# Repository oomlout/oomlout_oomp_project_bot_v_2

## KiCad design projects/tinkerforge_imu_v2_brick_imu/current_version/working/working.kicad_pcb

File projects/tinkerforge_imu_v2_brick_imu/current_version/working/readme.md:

# imu_v2_brick
 
## summary 
* id: tinkerforge_imu_v2_brick_imu
* user: tinkerforge
* name: imu_v2_brick
* board: imu
* repo: https://github.com/Tinkerforge/imu-v2-brick
* src_file_repo_kicad_pcb: hardware/V3/imu.kicad_pcb
* src_file_repo_kicad_pcb_link: https://github.com/Tinkerforge/imu-v2-brick/tree/master/hardware/V3/imu.kicad_pcb

* src_file_repo_sch: 
* src_file_repo_sch_link: https://github.com/Tinkerforge/imu-v2-brick/tree/master/
* full details link: https://github.com/oomlout/oomlout_oomp_project_bot_v_2/tree/main/projects/tinkerforge_imu_v2_brick_imu/current_version/working

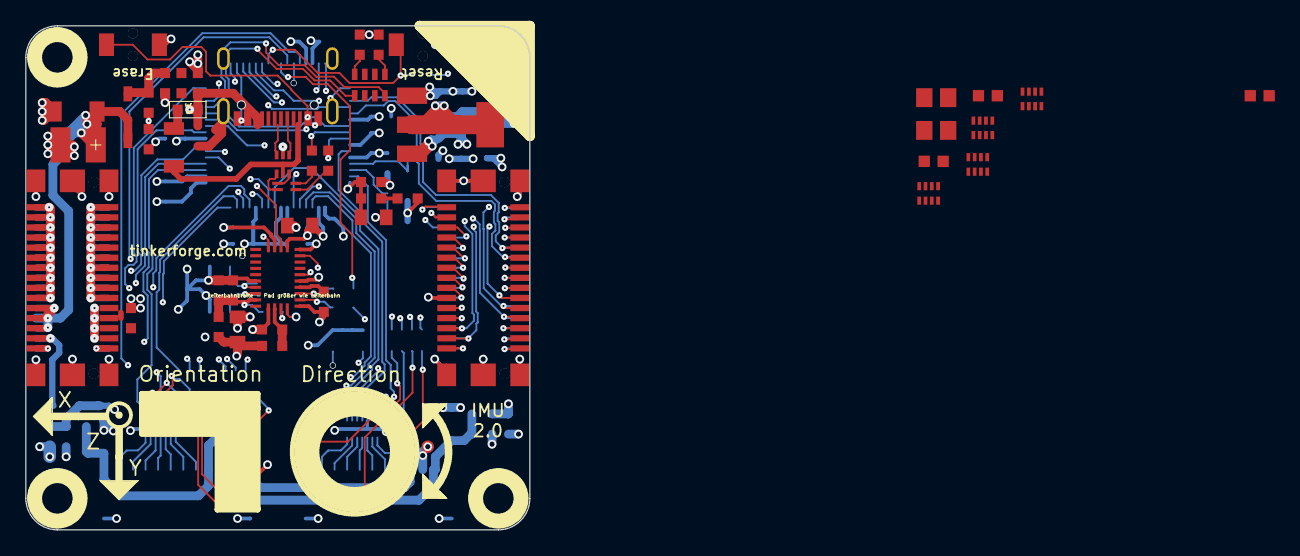
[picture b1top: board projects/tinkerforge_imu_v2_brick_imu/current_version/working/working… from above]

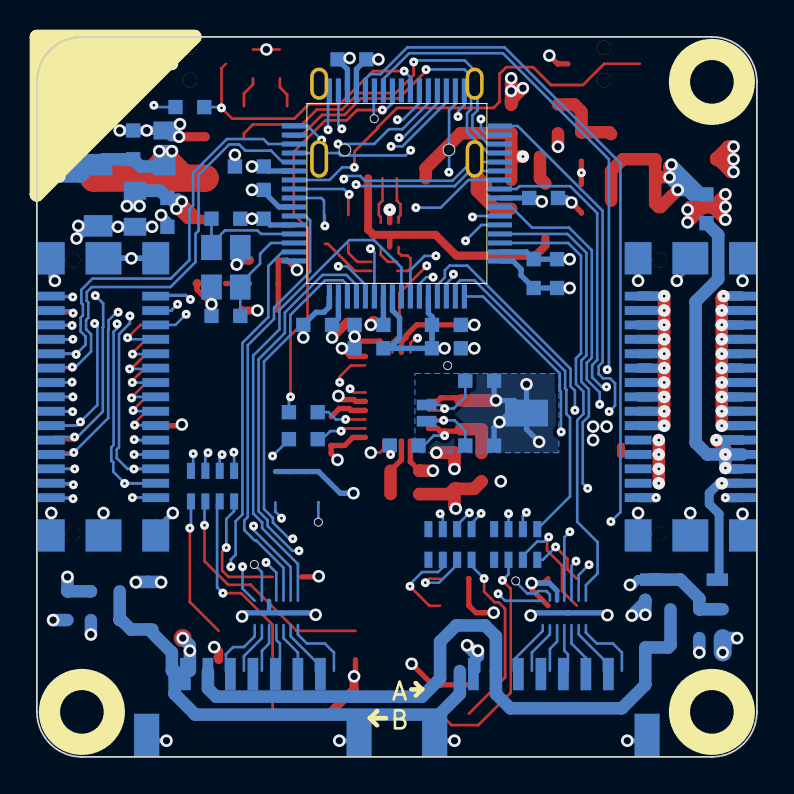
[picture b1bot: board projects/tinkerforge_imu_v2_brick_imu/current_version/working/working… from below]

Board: 4 copper layers, 40.0 x 40.0 mm, 96 parts (36 on the bottom side), 113 nets.

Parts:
C1, C2: DNP; C0603
C3: 1µF; 0603
C4: 1µF; C0603
C5, C6: 22pF; C0603
C7, C8, C14, C17, C18, C19, C20, C22, C23, C24, C26, C27, C29, C30: 100nF; C0603
C9: 6.8nF; C0603
C10: 120nF; C0603
C11: 4.7µF; C0805
C12: 100µF; 3528-21
C13, C16: 10µF; C0805
C15, C28: 4.7µF; C0603
C21: 2.2µF; C0603
C25: 10µF/10V; C0805
C31, C33: 10uF; C0805E
C32, C34: 100nF; C0603F
CP1, CP2: 220pF; 4X0402
D1, D3, D5, D7: blue; D0603
D2, D4, D6, D8: red; D0603
D9, D10, D11, D12: green; D0603
D13, D14: B0520LW-7-F; SOD-123
D15: Z5V; MiniMelf
D16: Z3.3V; MiniMelf
F1: PTC; C1206
FB1, FB3, FB4: FB; C0603
J1: USB-C
J2, J3, J4, J5: DRILL; DRILL_NP
J6, J8: STACK-UP-LOW; BTB08-ACS-TOP
J7, J9: STACK-DOWN; BTB08-ACS-BTM
L1: 744230900; WE-CNSW-0603
L2, L3: INDUCTOR; C0603
L4: LBR2012T100K; C0805
P1, P2: CON-SENSOR2
R1, R2: 27; R0603
R3: 0; R0603
R4: 47k; R0603
R5: 68k; R0603
R6: 10k; R0603
R7, R8: DNP; R0603
R9: 1k; R0603
R10: 1R0; R0603
R11: 56k; R0603F
RP1, RP2, RP3, RP4: 1k; 0603X4
RP5, RP6: 82; 4X0402
SW1: Reset; TACT-SWITCH
SW2: Erase; TACT-SWITCH
U1: AT91SAM3SXB; LQFP64
U2: 82400152; SOT563-SPEC
U3: BNO055; LGA28_5832
U4: LD1117; SOT-223
X1: 16Mhz; CRYSTAL_3225
X2: 32.768kHz; AB26TRQ

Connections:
3V3: C11.1, C13.1, C14.1, C15.1, C17.1, C19.1, C20.1, C25.1, C27.1, C30.1, C33.1, C34.1, D1.1, D2.1, D3.1, D4.1, D5.1, D6.1, D7.1, D8.1, D9.1, D10.1, D11.1, D12.1, D13.1, D16.2, J6.20, L2.2, L3.2, P1.3, P2.3, SW2.2, U1.1, U1.7, U1.18, U1.45, U1.58, U4.2
AGND: C3.2, J1.5, R3.2, U2.2
BNO-ADR-SELECT: U1.34, U3.17
BNO-BOOT: R6.2, U1.38, U3.4
BNO-INT: U1.26, U3.14
BNO-PIN7: R7.1, U1.52
BNO-PIN8: R8.1, U1.41
BNO-nRESET: U1.35, U3.11
GND: C1.2, C2.2, C4.2, C5.2, C6.2, C7.2, C8.2, C9.2, C10.2, C11.2, C12.2, C13.2, C14.2, C15.2, C16.2, C17.2, C18.2, C19.2, C20.2, C21.2, C22.2, C23.2, C24.2, C25.2, C26.2, C27.2, C28.2, C29.2, C30.2, C31.2, C32.2, C33.2, C34.2, CP1.5, CP1.6, CP1.7, CP1.8, CP2.5, CP2.6, CP2.7, CP2.8, D15.1, D16.1, FB3.1, J6.EP, J7.EP, J8.EP, J9.EP, P1.2, P1.EP, P2.2, P2.EP, R3.1, R5.1, SW1.2, U1.2, U1.17, U1.43, U1.46, U1.60, U3.2, U3.5, U3.6, U3.10, U3.15, U3.16, U3.18, U3.25, U4.1, X1.3, X2.3
LED-DEG-1: RP4.1, U1.20
LED-DEG-2: RP4.3, U1.37
LED-DEG-3: RP4.4, U1.48
LED-DEG-4: RP4.2, U1.32
LED-XYZ-XA: RP2.1, U1.15
LED-XYZ-XB: RP2.2, U1.13
LED-XYZ-YA: RP2.3, U1.23
LED-XYZ-YB: RP3.1, U1.16
LED-XYZ-ZA: RP3.2, U1.25
LED-XYZ-ZB: RP3.3, U1.42
unnamed: C3.1, F1.2, FB1.2
unnamed: C5.1, U3.27, X2.2
unnamed: C6.1, U3.26, X2.1
unnamed: C7.1, U3.9
unnamed: C8.1, L3.1, U3.3
unnamed: C9.1, C10.1, L2.1, R6.1, U3.28
unnamed: C21.1, C22.1, C23.1, C24.1, C26.1, L4.1, U1.8, U1.12, U1.24, U1.54
unnamed: C28.1, R10.1
unnamed: C29.1, L4.2, R10.2, U1.64
unnamed: CP1.1, P1.4, RP5.8
unnamed: CP1.2, P1.5, RP5.7
unnamed: CP1.3, P1.6, RP5.6
unnamed: CP2.1, P2.4, RP6.8
unnamed: CP2.2, P2.5, RP6.7
unnamed: CP2.3, P2.6, RP6.6
unnamed: D1.2, RP1.1
unnamed: D2.2, RP1.4
unnamed: D3.2, RP2.8
unnamed: D4.2, RP2.7
unnamed: D5.2, RP2.6
unnamed: D6.2, RP3.8
unnamed: D7.2, RP3.7
unnamed: D8.2, RP3.6
unnamed: D9.2, RP4.8
unnamed: D10.2, RP4.7
unnamed: D11.2, RP4.6
unnamed: D12.2, RP4.5
unnamed: D13.2, J8.28, J9.28
unnamed: F1.1, J1.1, R11.2, U2.5
unnamed: FB3.2, J8.21, J8.23, J8.25, J8.27, J9.21, J9.23, J9.25, J9.27
unnamed: FB4.1, J8.22, J8.24, J8.26, J9.22, J9.24, J9.26
unnamed: J1.2, U2.1
unnamed: J1.3, U2.3
unnamed: J1.4, R11.1
unnamed: J6.6, J7.8
unnamed: J6.7, J7.7, R9.1
unnamed: J6.8, J7.10
unnamed: J6.10, J7.12
unnamed: J6.12, J7.14
unnamed: J6.13, J7.13
unnamed: J6.14, J7.16
unnamed: J6.15, J7.15
unnamed: J6.16, J7.18
unnamed: J6.17, J7.17
unnamed: J6.18, J7.20
unnamed: J6.22, J7.22
unnamed: J6.24, J7.24
unnamed: J6.25, J7.25
unnamed: J6.27, J7.27
unnamed: J6.29, J7.29
unnamed: J6.30, J7.30
unnamed: J8.1, J8.3, J8.5, J8.7, J8.9, J8.11, J8.13, J8.15, J8.17, J8.19, J9.1, J9.3, J9.5, J9.7, J9.9, J9.11, J9.13, J9.15, J9.17, J9.19
unnamed: J8.2, J8.4, J8.6, J8.8, J8.10, J8.12, J8.14, J8.16, J8.18, J8.20, J9.2, J9.4, J9.6, J9.8, J9.10, J9.12, J9.14, J9.16, J9.18, J9.20
unnamed: J8.29, J9.29
unnamed: J8.30, J9.30
unnamed: L1.1, R2.1
unnamed: L1.2, U2.4
unnamed: L1.3, U2.6
unnamed: L1.4, R1.1
unnamed: P1.7, RP5.5
unnamed: P2.7, RP6.5
unnamed: R1.2, U1.56
unnamed: R2.2, U1.57
unnamed: R7.2, U3.7
unnamed: R8.2, U3.8
unnamed: RP1.5, U1.29
unnamed: RP1.8, U1.30
unnamed: SW2.1, U1.55
Port-A-CS: RP5.1, U1.4
Port-A-MISO: RP5.4, U1.19
Port-A-MOSI: RP5.3, U1.44
Port-B-CLK: RP6.2, U1.59
Port-B-CS: RP6.1, U1.3
Port-B-MISO: RP6.4, U1.9
Port-B-MOSI: RP6.3, U1.47
STACK-DETECT/JTAG-TMS: J6.9, J7.9, U1.51
STACK-I2C-SCL/JTAG-TDO: J6.4, J7.4, U1.49
STACK-I2C-SDA/JTAG-TDI: J6.2, J7.2, U1.33
STACK-INT0: J6.19, J7.19, U1.6
STACK-INT1: J6.21, J7.21, U1.31
STACK-INT2: J6.23, J7.23, U1.10
STACK-RESET: R9.2, SW1.1, U1.39
STACK-SER-RXD: J6.26, J7.26, U1.11
STACK-SER-TXD: J6.28, J7.28, U1.14
STACK-SPI-MISO: J6.1, J7.1, U1.27
STACK-SPI-MOSI: J6.3, J7.3, U1.22
STACK-SPI-SCLK: J6.5, J7.5, U1.21
STACK-SPI-SELECT: J7.6, U1.28
STACK-SYNC/JTAG-TCK: J6.11, J7.11, U1.53
USB-DETECT: R4.1, R5.2, U1.5
VSTACK: C12.1, C16.1, C18.1, C31.1, C32.1, D14.2, D15.2, FB4.2, P1.1, P2.1, U4.3
VUSB: C4.1, D14.1, FB1.1, R4.2
XIN: C2.1, U1.62, X1.2
XOUT: C1.1, U1.61, X1.1

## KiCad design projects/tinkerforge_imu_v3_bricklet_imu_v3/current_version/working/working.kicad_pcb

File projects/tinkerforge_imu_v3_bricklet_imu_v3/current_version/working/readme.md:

# imu_v3_bricklet
 
## summary 
* id: tinkerforge_imu_v3_bricklet_imu_v3
* user: tinkerforge
* name: imu_v3_bricklet
* board: imu_v3
* repo: https://github.com/Tinkerforge/imu-v3-bricklet
* src_file_repo_kicad_pcb: hardware/imu-v3.kicad_pcb
* src_file_repo_kicad_pcb_link: https://github.com/Tinkerforge/imu-v3-bricklet/tree/master/hardware/imu-v3.kicad_pcb

* src_file_repo_sch: hardware/imu-v3.sch
* src_file_repo_sch_link: https://github.com/Tinkerforge/imu-v3-bricklet/tree/master/hardware/imu-v3.sch
* full details link: https://github.com/oomlout/oomlout_oomp_project_bot_v_2/tree/main/projects/tinkerforge_imu_v3_bricklet_imu_v3/current_version/working

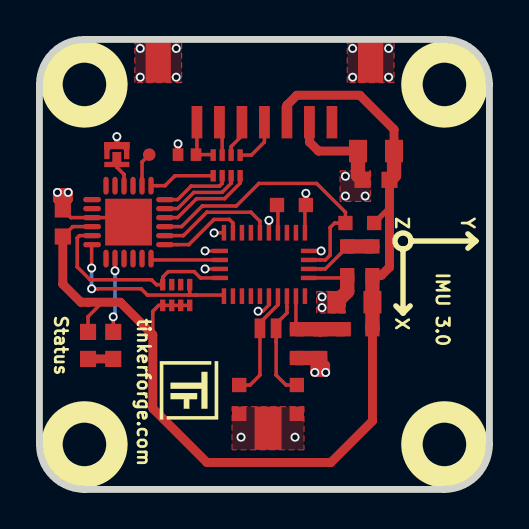
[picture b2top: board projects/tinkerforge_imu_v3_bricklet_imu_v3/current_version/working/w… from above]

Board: 2 copper layers, 25.0 x 25.0 mm, 30 parts (2 on the bottom side), 25 nets.

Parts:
C1: 220pF; C0402F
C2: 10uF; C0805
C3: 1uF; C0603F
C4, C5: 22pF; C0603
C6: 100nF; C0603F
C7, C8: 100nF; C0603
C9: 6.8nF; C0603
C10: 120nF; C0603
C11: 4.7µF; C0805
D1: blue; D0603F
L1, L2: INDUCTOR; C0603
P1: CON-SENSOR2
P2: BOOT; SolderJumper
P3: DEBUG; DEBUG_PAD
R1: 10k; R0603
R3: 1k; R0603F
RP1: 82; 4X0402
RP2: 3,9k; 4X0402
U1: XMC1302; QFN24-4x4mm-0.5mm
U2: BNO055; LGA28_5832
U3, U4, U5, U6: DRILL; DRILL_NP
VAL: CE_5mm
VAL#2: WEEE_7mm
X1: 32.768kHz; AB26TRQ

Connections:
BNO-ADR-SELECT: U1.18, U2.17
BNO-BOOT: R1.2, U1.21, U2.4
BNO-I2C-SCL: RP2.4, U1.11, U2.19
BNO-I2C-SDA: RP2.1, U1.12, U2.20
BNO-INT: U1.19, U2.14
BNO-nRESET: U1.20, U2.11
GND: C1.2, C2.2, C3.2, C4.2, C5.2, C6.2, C7.2, C8.2, C9.2, C10.2, C11.2, P1.2, P1.EP, P2.1, U1.9, U1.EXP, U2.2, U2.5, U2.6, U2.10, U2.15, U2.16, U2.18, U2.25, X1.3
unnamed: C1.1, P1.7, RP1.4
unnamed: C4.1, U2.27, X1.1
unnamed: C5.1, U2.26, X1.2
unnamed: C7.1, U2.9
unnamed: C8.1, L2.2, U2.3
unnamed: C9.1, C10.1, L1.2, U2.28
unnamed: D1.2, R3.2
unnamed: P1.4, RP1.1
unnamed: P1.5, RP1.2
unnamed: P1.6, RP1.3
unnamed: P2.2, U1.4
unnamed: P3.1, U1.2
unnamed: R3.1, U1.14
S-CLK: RP1.7, U1.23
S-CS: RP1.8, U1.22
S-MISO: RP1.5, U1.1
S-MOSI: RP1.6, U1.24
VCC: C2.1, C3.1, C6.1, C11.1, D1.1, L1.1, L2.1, P1.3, R1.1, RP2.5, RP2.6, RP2.7, RP2.8, U1.10

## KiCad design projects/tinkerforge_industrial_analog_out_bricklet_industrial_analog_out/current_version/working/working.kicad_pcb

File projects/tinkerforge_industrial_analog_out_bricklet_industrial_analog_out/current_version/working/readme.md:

# industrial_analog_out_bricklet
 
## summary 
* id: tinkerforge_industrial_analog_out_bricklet_industrial_analog_out
* user: tinkerforge
* name: industrial_analog_out_bricklet
* board: industrial_analog_out
* repo: https://github.com/Tinkerforge/industrial-analog-out-bricklet
* src_file_repo_kicad_pcb: hardware/industrial-analog-out.kicad_pcb
* src_file_repo_kicad_pcb_link: https://github.com/Tinkerforge/industrial-analog-out-bricklet/tree/master/hardware/industrial-analog-out.kicad_pcb

* src_file_repo_sch: hardware/industrial-analog-out.sch
* src_file_repo_sch_link: https://github.com/Tinkerforge/industrial-analog-out-bricklet/tree/master/hardware/industrial-analog-out.sch
* full details link: https://github.com/oomlout/oomlout_oomp_project_bot_v_2/tree/main/projects/tinkerforge_industrial_analog_out_bricklet_industrial_analog_out/current_version/working

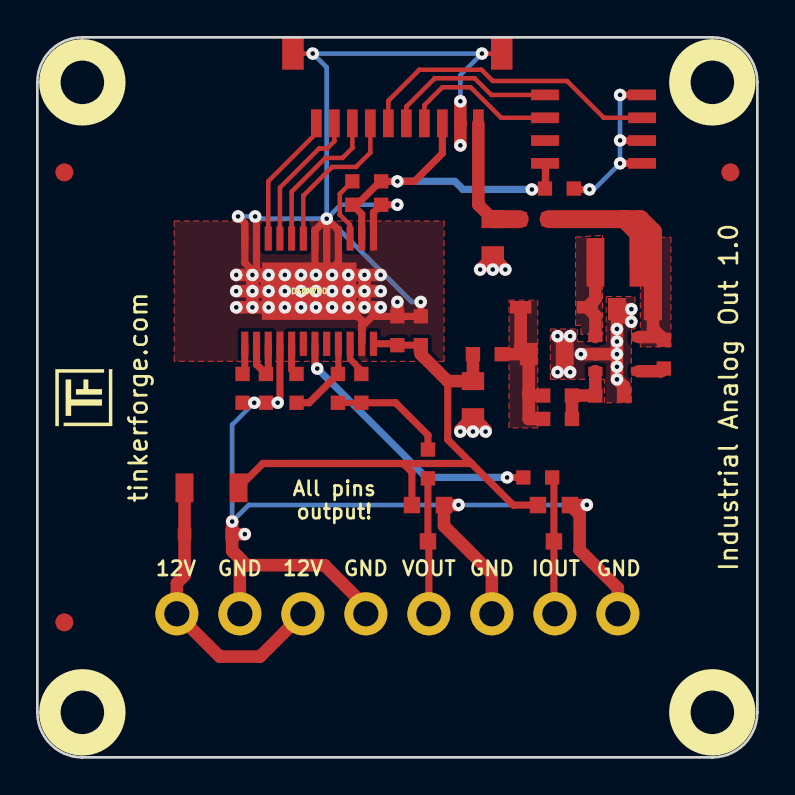
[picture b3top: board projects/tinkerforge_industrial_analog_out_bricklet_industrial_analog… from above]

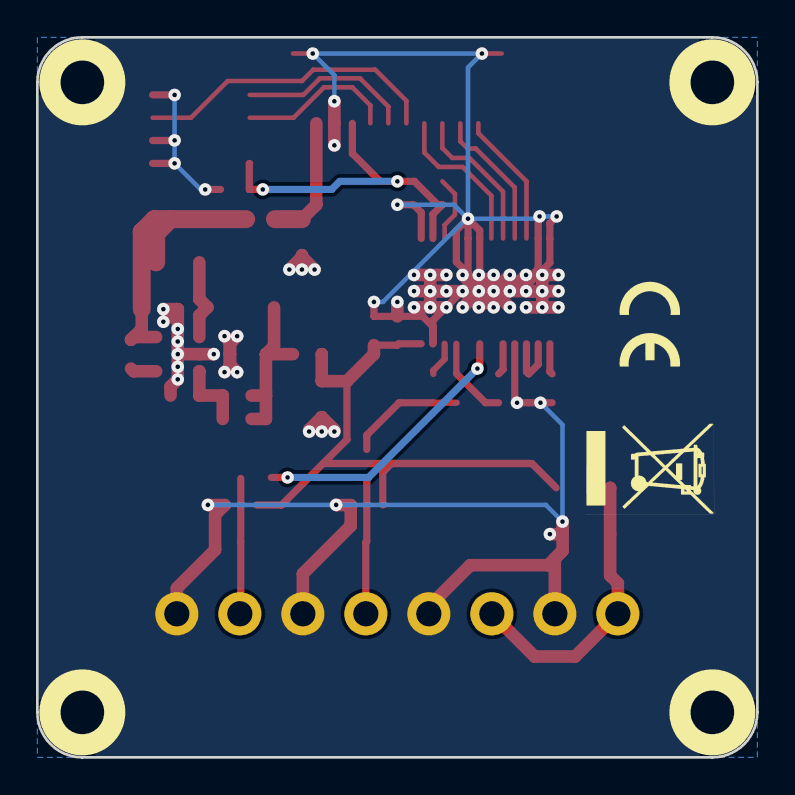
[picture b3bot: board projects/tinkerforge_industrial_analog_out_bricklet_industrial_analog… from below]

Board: 2 copper layers, 40.0 x 40.0 mm, 42 parts (2 on the bottom side), 27 nets.

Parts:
C1, C2, C5, C7: 4.7µF; C0805
C3, C6, C8, C9: 100nF; C0603
C4: 270pF; C0603
C10: 100pF; C0603
C11: 1nF; C0603
D1: B0520LW; SOD-123
D2, D3: DESD1P0RFW; SOT23-3
D4: CDSOD323-T15SC; SOD-323
F1: OZCJ0035FF2G; C1206
Fiducial_Mark: VAL**; Fiducial_Mark
Fiducial_Mark#2, Fiducial_Mark#3: VAL**; Fiducial_Mark
L1, L3, L4: FB; C0603
L2: 10µH; NR3030
P1: CON-SENSOR
P2: CONN_8; OQ_8P
R1: 1M; R0603
R2: 13.3k; R0603
R3: 118k; R0603
R4: 10k; R0603
R5: DNP; R0603
R6, R7: 15; R0603
R8: 10; R0603
U1: LMR62014X; SOT23-5
U2: M24C64; SOIC8
U3: DACX760; TSSOP24-44-PWR
U4, U5, U6, U7: DRILL; DRILL_NP
VAL: WEEE_7mm_back
VAL#2: CE_5mm

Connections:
3V3: C3.1, C6.1, P1.3, R4.1, U2.8, U3.2
+5V: C1.2, L1.2, P1.1
+12V: C7.2, C9.2, C10.2, D2.2, D3.2, F1.1, L3.1, U3.24
GND: C1.1, C2.1, C3.2, C5.1, C6.2, C7.1, C8.2, C9.1, C10.1, D2.1, D3.1, D4.2, P1.2, P1.EP, P2.2, P2.4, P2.6, P2.8, R2.2, R5.2, U1.2, U2.1, U2.2, U2.4, U3.1, U3.4, U3.5, U3.6, U3.11, U3.12, U3.16, U3.23
unnamed: C2.2, L1.1, L2.2, R1.1, U1.5
unnamed: C4.1, C5.2, D1.2, L3.2, R3.1
unnamed: C4.2, R2.1, R3.2, U1.3
unnamed: C8.1, U3.14, U3.15
unnamed: C11.1, R7.2, U3.21
unnamed: C11.2, U3.17
unnamed: D1.1, L2.1, U1.1
unnamed: D2.3, L4.1, P2.5
unnamed: D3.3, P2.7, R8.1
unnamed: D4.1, F1.2, P2.1, P2.3
unnamed: L4.2, R6.1, R7.1
unnamed: P1.4, U2.6
unnamed: P1.5, U2.5
unnamed: P1.6, U2.3
unnamed: P1.7, U3.7
unnamed: P1.8, U3.8
unnamed: P1.9, U3.9
unnamed: P1.10, U3.10
unnamed: R1.2, U1.4
unnamed: R4.2, U3.3
unnamed: R5.1, U3.13
unnamed: R6.2, U3.22
unnamed: R8.2, U3.19

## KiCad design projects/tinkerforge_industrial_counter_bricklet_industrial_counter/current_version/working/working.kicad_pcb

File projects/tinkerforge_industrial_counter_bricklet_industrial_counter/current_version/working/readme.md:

# industrial_counter_bricklet
 
## summary 
* id: tinkerforge_industrial_counter_bricklet_industrial_counter
* user: tinkerforge
* name: industrial_counter_bricklet
* board: industrial_counter
* repo: https://github.com/Tinkerforge/industrial-counter-bricklet
* src_file_repo_kicad_pcb: hardware/industrial-counter.kicad_pcb
* src_file_repo_kicad_pcb_link: https://github.com/Tinkerforge/industrial-counter-bricklet/tree/master/hardware/industrial-counter.kicad_pcb

* src_file_repo_sch: hardware/industrial-counter.sch
* src_file_repo_sch_link: https://github.com/Tinkerforge/industrial-counter-bricklet/tree/master/hardware/industrial-counter.sch
* full details link: https://github.com/oomlout/oomlout_oomp_project_bot_v_2/tree/main/projects/tinkerforge_industrial_counter_bricklet_industrial_counter/current_version/working

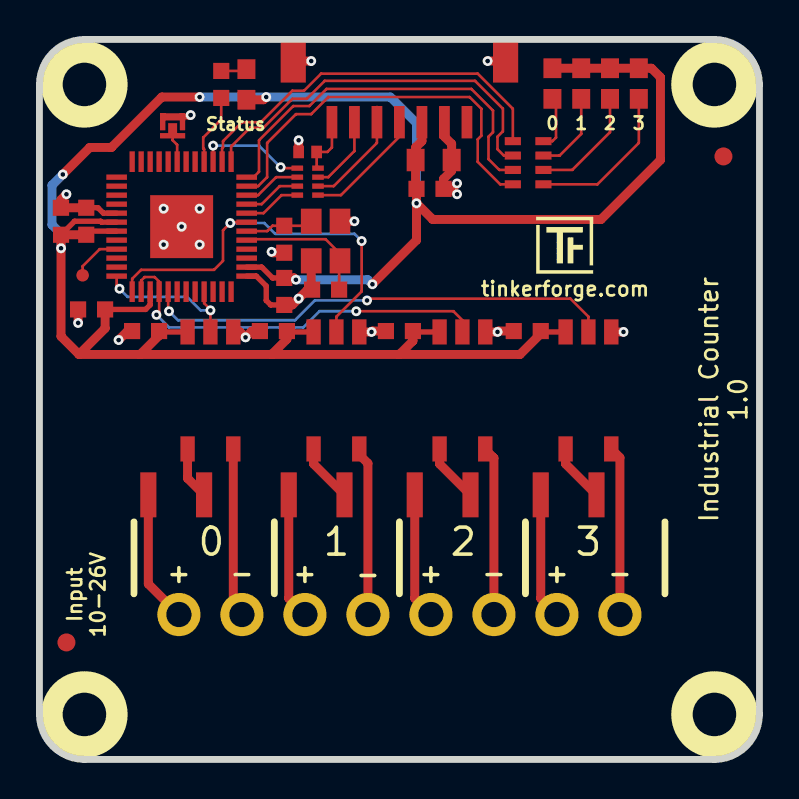
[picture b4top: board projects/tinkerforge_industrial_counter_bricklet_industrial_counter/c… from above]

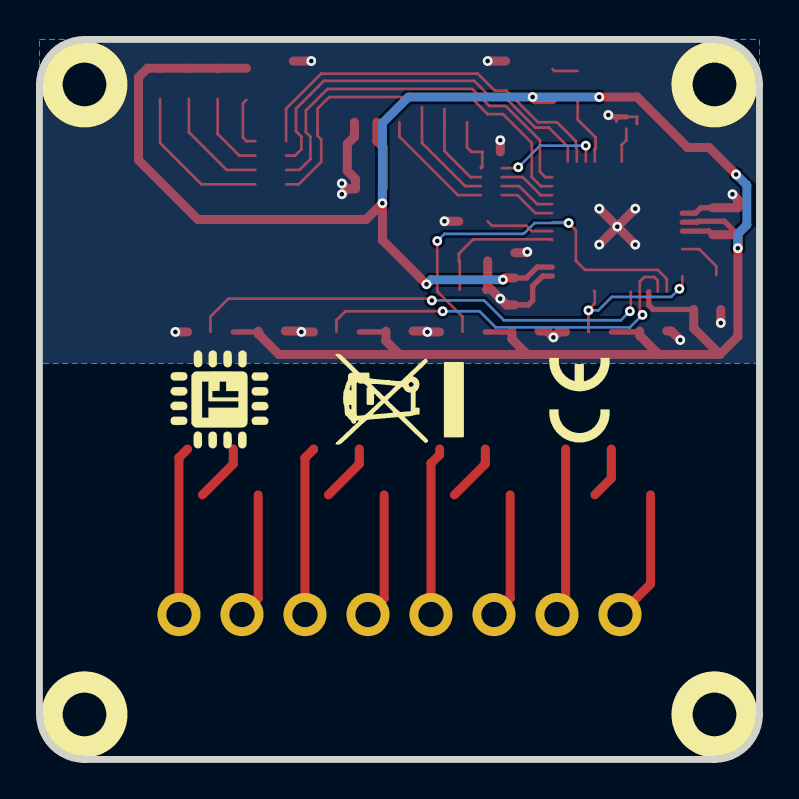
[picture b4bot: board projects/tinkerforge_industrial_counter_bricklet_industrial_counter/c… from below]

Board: 2 copper layers, 40.0 x 40.0 mm, 43 parts (2 on the bottom side), 40 nets.

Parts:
C1: 220pF; C0402F
C2: 10uF; C0805
C3: 1uF; C0603F
C4, C5: 10pF; C0603F
C6, C7, C8, C10, C11, C12, C13: 100nF; C0603F
C9: 220nF; C0603F
D1, D2, D3, D4, D5: blue; D0603E
Fiducial_Mark: VAL**; Fiducial_Mark
Fiducial_Mark#2: VAL**; Fiducial_Mark
J1: DEBUG; DEBUG_PAD
P1: CON-SENSOR2
P2: BOOT; SolderJumper
P3: CONN_8; OQ_8P
R1: 1k; R0603F
R2, R3, R4, R5: 2.7k 0.5W; R1210
RP1: 82; 4X0402
RP2: 1k; 0603X4
U1: XMC1404; QFN48-EP2
U2, U3, U4, U5: TLP2367; SO-5
U6, U7, U8, U9: DRILL; DRILL_NP
VAL: CE_5mm
VAL#2: WEEE_7mm
X1: 16MHz; CRYSTAL_3225

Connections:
GND: C1.2, C2.1, C3.1, C4.2, C5.2, C6.2, C7.2, C8.2, C9.2, C10.2, C11.2, C12.2, C13.2, P1.2, P1.EP, P2.1, U1.17, U1.37, U1.EP, U2.4, U3.4, U4.4, U5.4, X1.3
IN1: U1.24, U1.33, U2.5
IN2: U1.25, U1.43, U3.5
IN3: U1.26, U1.28, U4.5
IN4: U1.29, U5.5
unnamed: C1.1, P1.7, RP1.4
unnamed: C4.1, U1.41, X1.2
unnamed: C5.1, U1.42, X1.1
unnamed: D1.2, R1.2
unnamed: D2.2, RP2.8
unnamed: D3.2, RP2.7
unnamed: D4.2, RP2.6
unnamed: D5.2, RP2.5
unnamed: J1.1, U1.21
unnamed: P1.4, RP1.1
unnamed: P1.5, RP1.2
unnamed: P1.6, RP1.3
unnamed: P2.2, U1.7
unnamed: P3.1, R2.1
unnamed: P3.2, U2.3
unnamed: P3.3, R3.1
unnamed: P3.4, U3.3
unnamed: P3.5, R4.1
unnamed: P3.6, U4.3
unnamed: P3.7, R5.1
unnamed: P3.8, U5.3
unnamed: R1.1, U1.4
unnamed: R2.2, U2.1
unnamed: R3.2, U3.1
unnamed: R4.2, U4.1
unnamed: R5.2, U5.1
S-CLK: RP1.7, U1.45
S-CS: RP1.8, U1.44
S-MISO: RP1.5, U1.3
S-MOSI: RP1.6, U1.46
STATUS1: RP2.1, U1.2
STATUS2: RP2.2, U1.1
STATUS3: RP2.3, U1.48
STATUS4: RP2.4, U1.47
VCC: C2.2, C3.2, C6.1, C7.1, C8.1, C9.1, C10.1, C11.1, C12.1, C13.1, D1.1, D2.1, D3.1, D4.1, D5.1, P1.3, U1.18, U1.19, U1.27, U1.38, U2.6, U3.6, U4.6, U5.6

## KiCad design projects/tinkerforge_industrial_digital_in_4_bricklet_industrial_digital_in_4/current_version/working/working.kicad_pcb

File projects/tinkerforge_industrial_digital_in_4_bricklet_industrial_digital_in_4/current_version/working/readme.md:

# industrial_digital_in_4_bricklet
 
## summary 
* id: tinkerforge_industrial_digital_in_4_bricklet_industrial_digital_in_4
* user: tinkerforge
* name: industrial_digital_in_4_bricklet
* board: industrial_digital_in_4
* repo: https://github.com/Tinkerforge/industrial-digital-in-4-bricklet
* src_file_repo_kicad_pcb: hardware/industrial-digital-in-4.kicad_pcb
* src_file_repo_kicad_pcb_link: https://github.com/Tinkerforge/industrial-digital-in-4-bricklet/tree/master/hardware/industrial-digital-in-4.kicad_pcb

* src_file_repo_sch: hardware/industrial-digital-in-4.sch
* src_file_repo_sch_link: https://github.com/Tinkerforge/industrial-digital-in-4-bricklet/tree/master/hardware/industrial-digital-in-4.sch
* full details link: https://github.com/oomlout/oomlout_oomp_project_bot_v_2/tree/main/projects/tinkerforge_industrial_digital_in_4_bricklet_industrial_digital_in_4/current_version/working

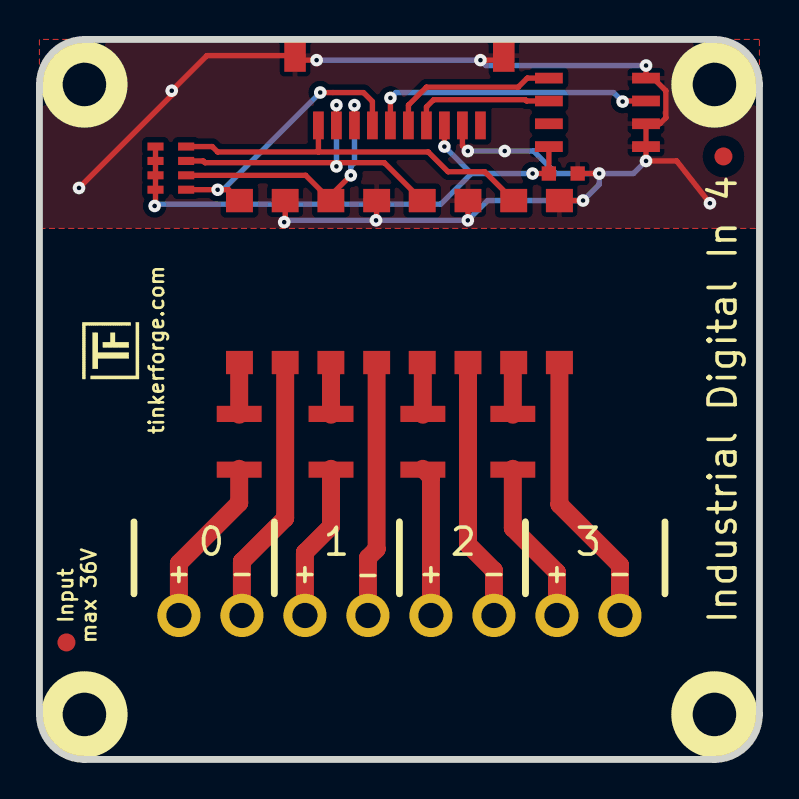
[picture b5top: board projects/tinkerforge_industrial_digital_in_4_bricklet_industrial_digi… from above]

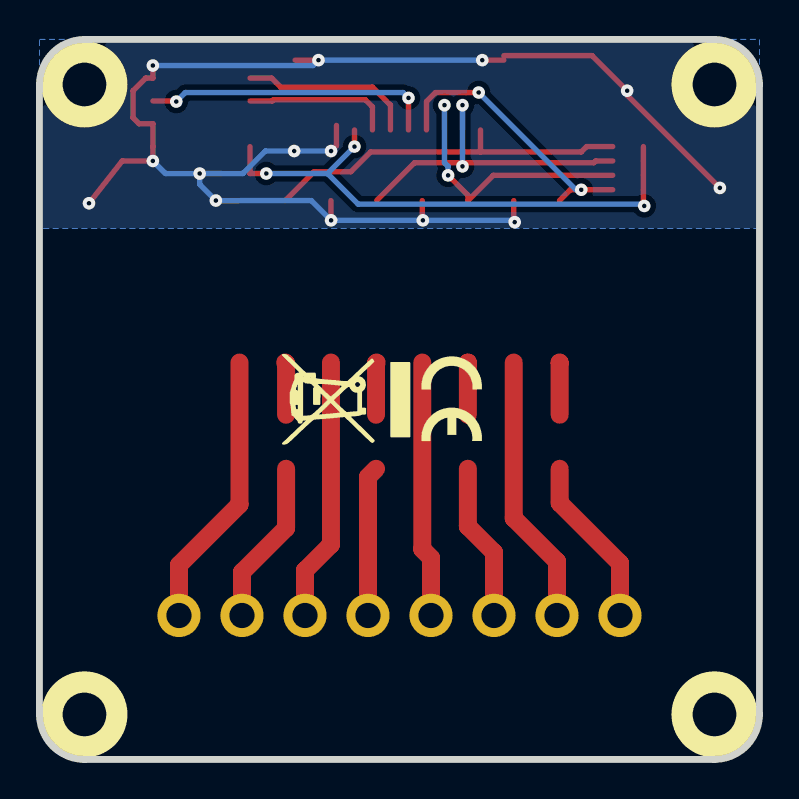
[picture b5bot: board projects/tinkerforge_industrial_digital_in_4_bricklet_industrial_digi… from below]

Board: 2 copper layers, 40.0 x 40.0 mm, 18 parts (2 on the bottom side), 21 nets.

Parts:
C1: 100nF; C0603
Fiducial_Mark: VAL**; Fiducial_Mark
Fiducial_Mark#2: VAL**; Fiducial_Mark
P1: CON-SENSOR
P2: Digital Input; OQ_8P
R1, R2, R3, R4: 4.7k; R1210
RP1: 10k; 0603X4
U1: M24C64; SOIC8
U2: LTV846S; OPTO-SMD16
U3, U4, U5, U6: DRILL; DRILL_NP
VAL: CE_5mm
VAL#2: WEEE_7mm

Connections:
3V3: C1.1, P1.3, RP1.5, RP1.6, RP1.7, RP1.8, U1.8
GND: C1.2, P1.2, P1.EP, U1.1, U1.2, U1.4, U2.9, U2.11, U2.13, U2.15
INPUT1: P1.7, RP1.1, U2.16
INPUT2: P1.8, RP1.2, U2.14
INPUT3: P1.9, RP1.3, U2.12
INPUT4: P1.10, RP1.4, U2.10
unnamed: P1.4, U1.6
unnamed: P1.5, U1.5
unnamed: P1.6, U1.3
unnamed: P2.1, R1.2
unnamed: P2.2, U2.2
unnamed: P2.3, R2.2
unnamed: P2.4, U2.4
unnamed: P2.5, R3.2
unnamed: P2.6, U2.6
unnamed: P2.7, R4.2
unnamed: P2.8, U2.8
unnamed: R1.1, U2.1
unnamed: R2.1, U2.3
unnamed: R3.1, U2.5
unnamed: R4.1, U2.7

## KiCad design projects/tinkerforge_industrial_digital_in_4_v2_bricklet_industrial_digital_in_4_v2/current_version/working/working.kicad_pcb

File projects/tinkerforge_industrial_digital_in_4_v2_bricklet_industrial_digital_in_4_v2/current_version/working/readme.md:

# industrial_digital_in_4_v2_bricklet
 
## summary 
* id: tinkerforge_industrial_digital_in_4_v2_bricklet_industrial_digital_in_4_v2
* user: tinkerforge
* name: industrial_digital_in_4_v2_bricklet
* board: industrial_digital_in_4_v2
* repo: https://github.com/Tinkerforge/industrial-digital-in-4-v2-bricklet
* src_file_repo_kicad_pcb: hardware/industrial-digital-in-4-v2.kicad_pcb
* src_file_repo_kicad_pcb_link: https://github.com/Tinkerforge/industrial-digital-in-4-v2-bricklet/tree/master/hardware/industrial-digital-in-4-v2.kicad_pcb
* src_file_repo_kicad_sch: hardware/industrial-digital-in-4-v2.kicad_sch
* src_file_repo_kicad_sch_link: https://github.com/Tinkerforge/industrial-digital-in-4-v2-bricklet/tree/master/hardware/industrial-digital-in-4-v2.kicad_sch

* src_file_repo_sch: 
* src_file_repo_sch_link: https://github.com/Tinkerforge/industrial-digital-in-4-v2-bricklet/tree/master/
* full details link: https://github.com/oomlout/oomlout_oomp_project_bot_v_2/tree/main/projects/tinkerforge_industrial_digital_in_4_v2_bricklet_industrial_digital_in_4_v2/current_version/working

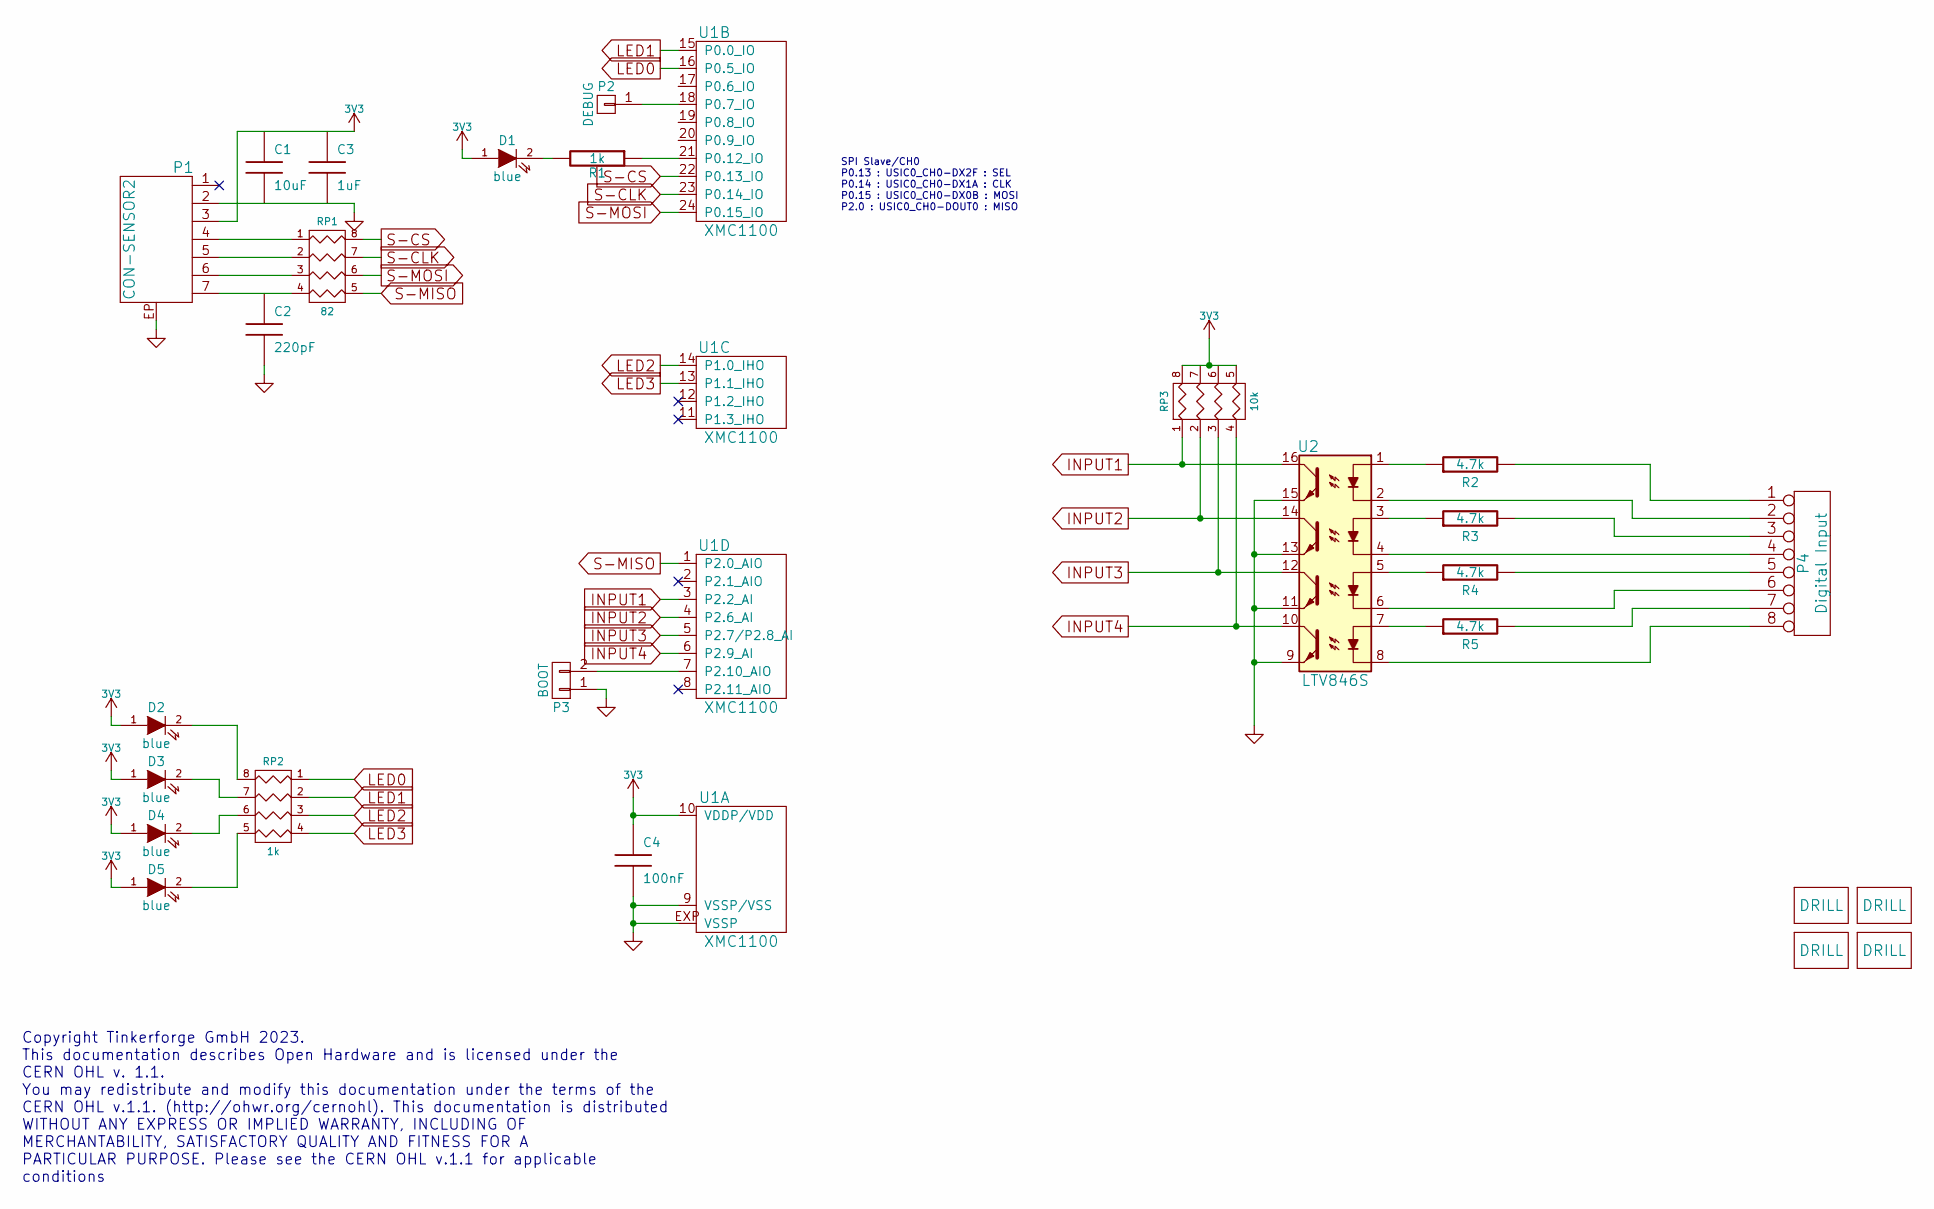
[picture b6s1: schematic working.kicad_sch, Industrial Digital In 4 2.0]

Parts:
C1: 10uF; C0805
C2: 220pF; C0402F
C3: 1uF; C0603F
C4: 100nF; C0603F
D1, D2, D3, D4, D5: blue; D0603F
P1: CON-SENSOR2
P2: DEBUG; DEBUG_PAD
P3: BOOT; SolderJumper
P4: Digital Input; OQ_8P
R1: 1k; R0603F
R2, R3, R4, R5: 4.7k; R1210
RP1: 82; 4X0402
RP2: 1k; 0603X4
RP3: 10k; 0603X4
U1: XMC1100; QFN24-4x4mm-0.5mm
U2: LTV846S; DIP-16
U3, U4, U5, U6: DRILL; DRILL_NP

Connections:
3V3: C1.1, C3.1, C4.1, D1.1 (A), D2.1 (A), D3.1 (A), D4.1 (A), D5.1 (A), P1.3, RP3.5 (R4), RP3.6 (R3), RP3.7 (R2), RP3.8 (R1), U1.10 (VDDP/VDD)
GND: C1.2, C2.2, C3.2, C4.2, P1.2, P1.EP, P3.1, U1.9 (VSSP/VSS), U1.EXP (VSSP), U2.9, U2.11, U2.13, U2.15
INPUT1: RP3.1, U1.3 (P2.2_AI), U2.16
INPUT2: RP3.2, U1.4 (P2.6_AI), U2.14
INPUT3: RP3.3, U1.5 (P2.7/P2.8_AI), U2.12
INPUT4: RP3.4, U1.6 (P2.9_AI), U2.10
LED0: RP2.1, U1.16 (P0.5_IO)
LED1: RP2.2, U1.15 (P0.0_IO)
LED2: RP2.3, U1.14 (P1.0_IHO)
LED3: RP2.4, U1.13 (P1.1_IHO)
unnamed: D1.2 (K), R1.2
unnamed: D2.2 (K), RP2.8 (R1)
unnamed: D3.2 (K), RP2.7 (R2)
unnamed: D4.2 (K), RP2.6 (R3)
unnamed: D5.2 (K), RP2.5 (R4)
unnamed: P1.4, RP1.1
unnamed: P1.5, RP1.2
unnamed: P1.6, RP1.3
unnamed: P2.1, U1.18 (P0.7_IO)
unnamed: P3.2, U1.7 (P2.10_AIO)
unnamed: P4.1, R2.2
unnamed: P4.2, U2.2
unnamed: P4.3, R3.2
unnamed: P4.4, U2.4
unnamed: P4.5, R4.2
unnamed: P4.6, U2.6
unnamed: P4.7, R5.2
unnamed: P4.8, U2.8
unnamed: R1.1, U1.21 (P0.12_IO)
unnamed: R2.1, U2.1
unnamed: R3.1, U2.3
unnamed: R4.1, U2.5
unnamed: R5.1, U2.7
S-CLK: RP1.7 (R2), U1.23 (P0.14_IO)
S-CS: RP1.8 (R1), U1.22 (P0.13_IO)
S-MISO: RP1.5 (R4), U1.1 (P2.0_AIO)
S-MOSI: RP1.6 (R3), U1.24 (P0.15_IO)

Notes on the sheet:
SPI Slave/CH0 P0.13 : USIC0_CH0-DX2F : SEL P0.14 : USIC0_CH0-DX1A : CLK P0.15 : USIC0_CH0-DX0B : MOSI P2.0 : USIC0_CH0-DOUT0 : MISO
Copyright Tinkerforge GmbH 2023. This documentation describes Open Hardware and is licensed under the CERN OHL v. 1.1. You may redistribute and modify this documentation under the terms of the CERN OHL v.1.1. (http://ohwr.org/cernohl). This documentation is distributed WITHOUT ANY EXPRESS OR IMPLIE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

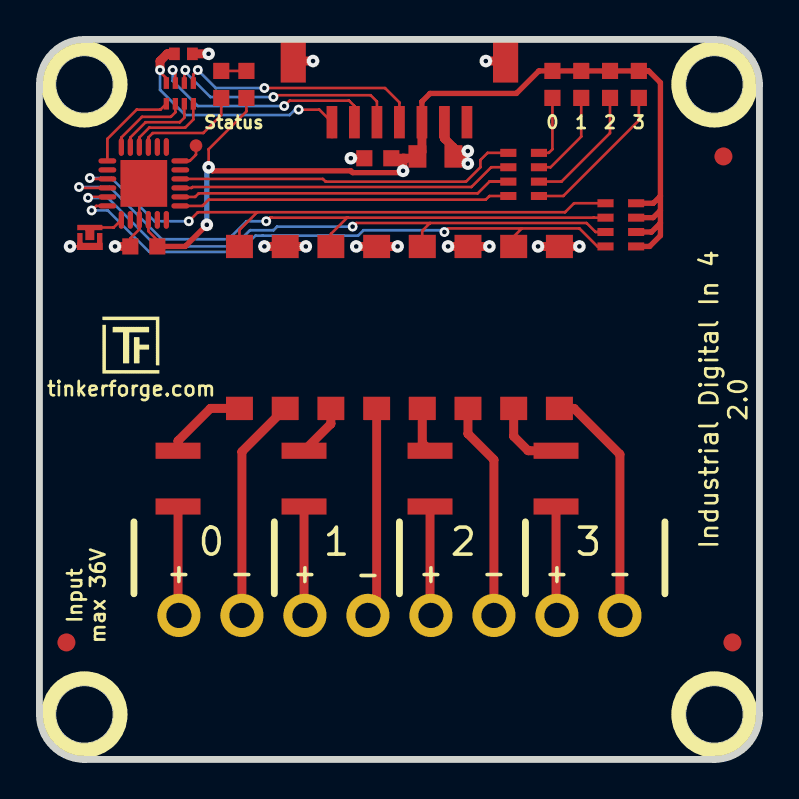
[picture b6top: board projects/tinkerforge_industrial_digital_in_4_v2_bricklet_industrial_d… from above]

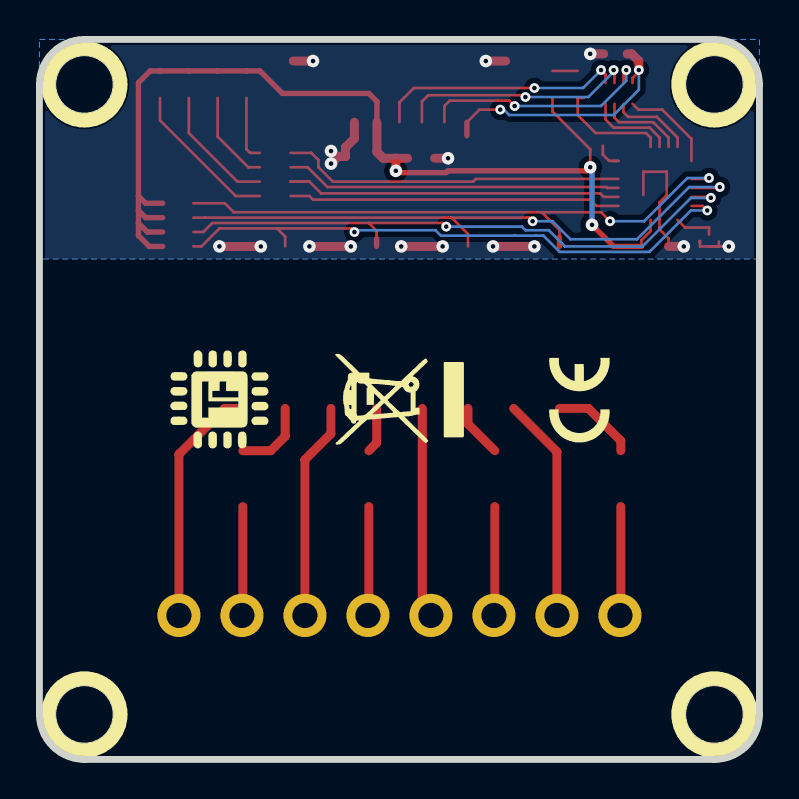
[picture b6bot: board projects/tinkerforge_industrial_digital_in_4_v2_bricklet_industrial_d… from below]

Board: 2 copper layers, 40.0 x 40.0 mm, 32 parts (2 on the bottom side), 38 nets.

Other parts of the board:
Fiducial_Mark: VAL**; Fiducial_Mark
Fiducial_Mark#2, Fiducial_Mark#3: VAL**; Fiducial_Mark
VAL: CE_5mm
VAL#2: WEEE_7mm

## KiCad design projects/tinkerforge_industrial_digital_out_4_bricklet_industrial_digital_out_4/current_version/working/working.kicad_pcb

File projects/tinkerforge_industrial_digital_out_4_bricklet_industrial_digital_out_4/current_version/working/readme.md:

# industrial_digital_out_4_bricklet
 
## summary 
* id: tinkerforge_industrial_digital_out_4_bricklet_industrial_digital_out_4
* user: tinkerforge
* name: industrial_digital_out_4_bricklet
* board: industrial_digital_out_4
* repo: https://github.com/Tinkerforge/industrial-digital-out-4-bricklet
* src_file_repo_kicad_pcb: hardware/industrial-digital-out-4.kicad_pcb
* src_file_repo_kicad_pcb_link: https://github.com/Tinkerforge/industrial-digital-out-4-bricklet/tree/master/hardware/industrial-digital-out-4.kicad_pcb

* src_file_repo_sch: hardware/industrial-digital-out-4.sch
* src_file_repo_sch_link: https://github.com/Tinkerforge/industrial-digital-out-4-bricklet/tree/master/hardware/industrial-digital-out-4.sch
* full details link: https://github.com/oomlout/oomlout_oomp_project_bot_v_2/tree/main/projects/tinkerforge_industrial_digital_out_4_bricklet_industrial_digital_out_4/current_version/working

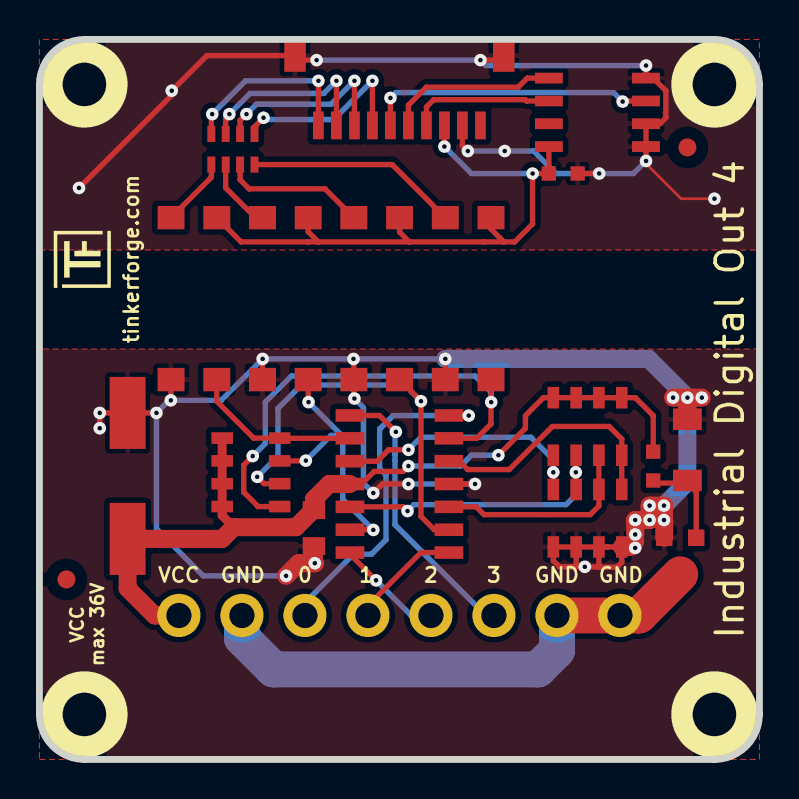
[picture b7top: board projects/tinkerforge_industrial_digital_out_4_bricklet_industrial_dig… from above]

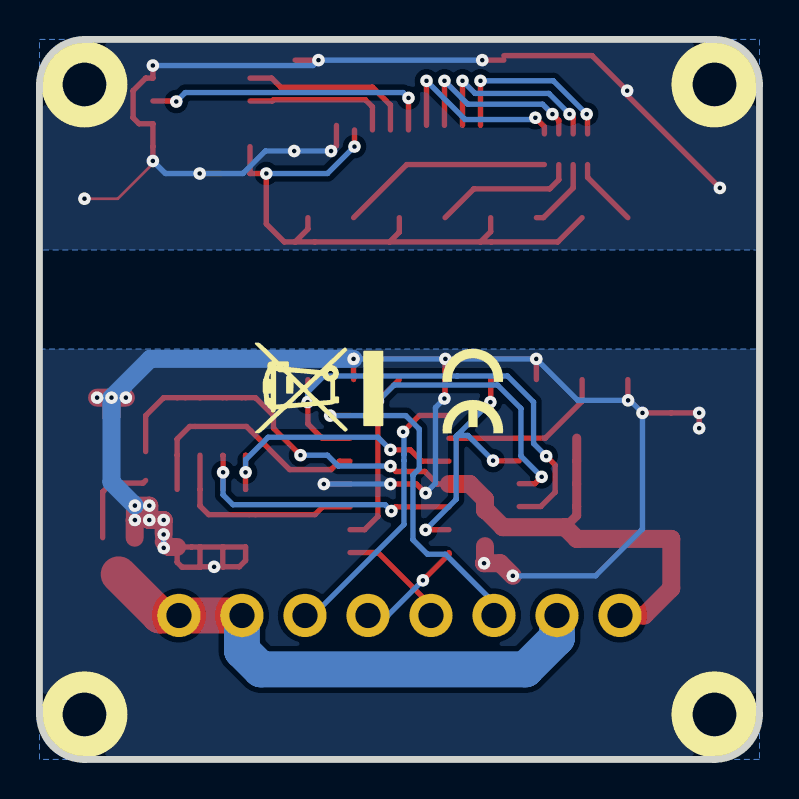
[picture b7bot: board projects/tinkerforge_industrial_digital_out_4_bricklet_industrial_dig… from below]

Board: 2 copper layers, 40.0 x 40.0 mm, 23 parts (2 on the bottom side), 29 nets.

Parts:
C1: 100nF; C0603
C2: 100nF; C0805
C3: 68µF/50V; ELKO_83
D1: Z12V; MiniMelf
Fiducial_Mark: VAL**; Fiducial_Mark
Fiducial_Mark#2: VAL**; Fiducial_Mark
P1: CON-SENSOR
P2: Digital Output; OQ_8P
Q1: FDN5630; SOT23GDS
R1: 100k; R0603
RP1: 1k; 0603X4
RP2: 12k; 1206X4
RP3, RP4: 10k; 1206X4
U1: M24C64; SOIC8
U2: LTV846S; OPTO-SMD16
U3: OPA4171AIDR; SOP14
U4, U5, U6, U7: DRILL; DRILL_NP
VAL: WEEE_7mm
VAL#2: CE_5mm

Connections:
3V3: C1.1, P1.3, U1.8, U2.1, U2.3, U2.5, U2.7
AGND: C2.2, C3.2, D1.1, Q1.S, RP4.1, RP4.2, RP4.3, RP4.4, U2.9, U2.11, U2.13, U2.15, U3.11
GND: C1.2, P1.2, P1.EP, U1.1, U1.2, U1.4
unnamed: D1.2, Q1.G, R1.2
unnamed: P1.4, U1.6
unnamed: P1.5, U1.5
unnamed: P1.6, U1.3
unnamed: P2.2, P2.7, P2.8, Q1.D
unnamed: P2.3, U3.14
unnamed: P2.4, U3.8
unnamed: P2.5, U3.7
unnamed: P2.6, U3.1
unnamed: RP1.5, U2.8
unnamed: RP1.6, U2.6
unnamed: RP1.7, U2.4
unnamed: RP1.8, U2.2
unnamed: RP2.1, U2.16, U3.13
unnamed: RP2.2, U2.14, U3.9
unnamed: RP2.3, U2.12, U3.6
unnamed: RP2.4, U2.10, U3.2
unnamed: RP3.1, RP4.8, U3.3
unnamed: RP3.2, RP4.7, U3.5
unnamed: RP3.3, RP4.6, U3.10
unnamed: RP3.4, RP4.5, U3.12
OUTPUT1: P1.7, RP1.1
OUTPUT2: P1.8, RP1.2
OUTPUT3: P1.9, RP1.3
OUTPUT4: P1.10, RP1.4
VPP: C2.1, C3.1, P2.1, R1.1, RP2.5, RP2.6, RP2.7, RP2.8, RP3.5, RP3.6, RP3.7, RP3.8, U3.4

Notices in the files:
projects/tinkerforge_imu_v2_brick_imu/current_version/working/working.kicad_pcb:
Licensed under CERN OHL v.1.1
Copyright (©) 2015, B.Nordmeyer
Copyright Tinkerforge GmbH 2015.
projects/tinkerforge_industrial_analog_out_v2_bricklet_industrial_analog_out_v2/current_version/working/working.kicad_sch:
Copyright (©) 2023, T.Schneidermann
projects/tinkerforge_industrial_counter_bricklet_industrial_counter/current_version/working/working.kicad_pcb:
Copyright (©) 2017, B.Nordmeyer
Copyright Tinkerforge GmbH 2017.
